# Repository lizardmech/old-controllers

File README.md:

# old-controllers
Footprints located in footprint.zip file unzip to same dir
Schematics are complete chaos may not resemble any of the actual designs, I just threw things into them and did most of the work in PCB editor.

All of these require external capacitors and usually a 15v powersupply in addition to primary supply.
horizontal & BJT PCB small 50mm x 100mm with 12 mosfets and allegro current sense. Probably works but has many less than ideal layout issues.

Sept PCB Large 2 layer PCB with isolated SI8920 current sensors, works very nicely however SI8920 needs complex opamps to be used with cheaper MCUs. Curremt sense on phase A + C. Causes issue with instaspin which expects phase A + B in 2 sensor mode. Lacks any enable or disable pin on gate drivers, attach power without MCU driving them low = bang!
Sept12 & gan same board with space for 12 mosfets and 12 GaNfets should work but untested.

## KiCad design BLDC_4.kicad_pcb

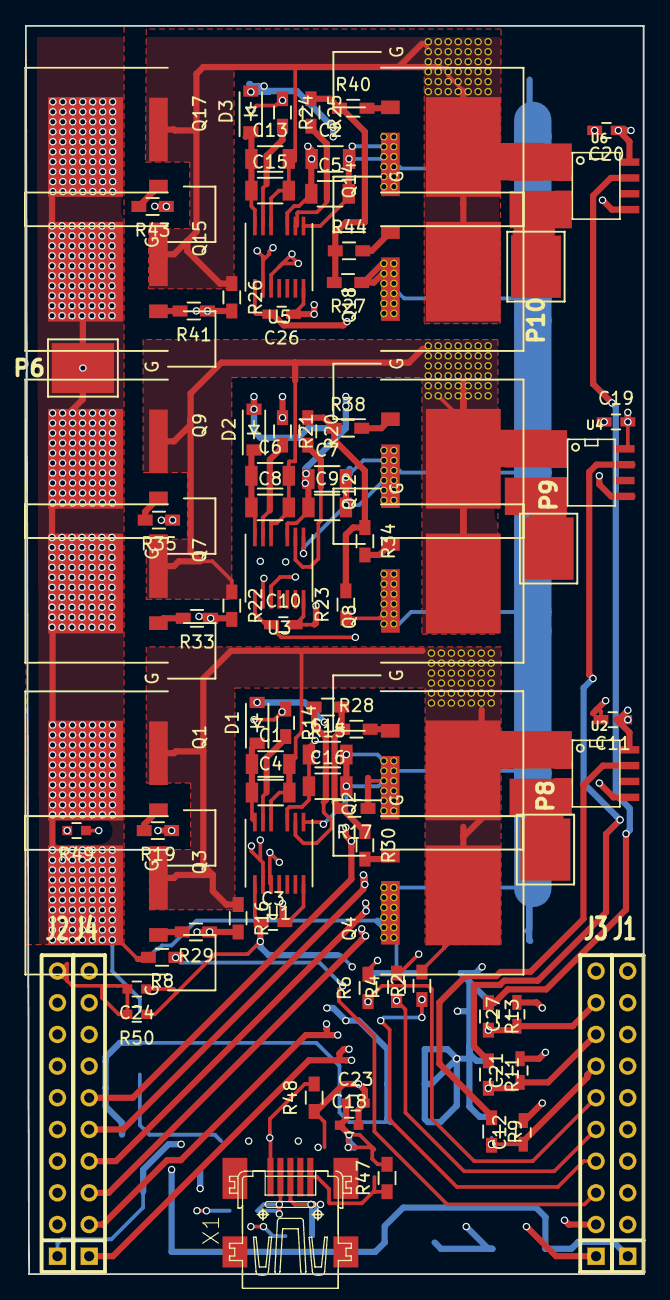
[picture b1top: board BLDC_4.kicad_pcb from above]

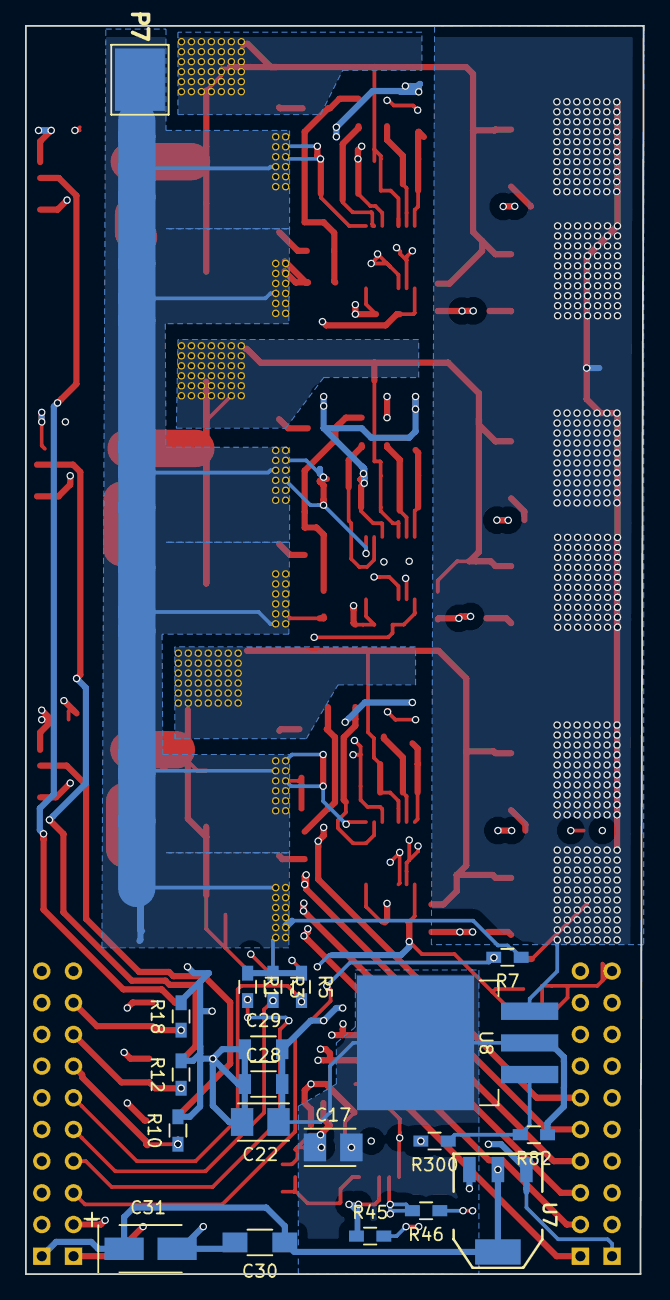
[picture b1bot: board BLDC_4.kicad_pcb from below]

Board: 4 copper layers, 49.5 x 100.1 mm, 109 parts (20 on the bottom side), 62 nets.

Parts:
C1, C2, C6, C7, C13, C14: 0.1uf; C_1206
C3, C10, C11, C12, C19, C20, C21, C26, C27: 0.1uf; C_0603_HandSoldering
C4, C5, C8, C9, C15, C16, C28, C29: 10uf; C_1206
C17, C22: 100uf; TantalC_SizeB_EIA-3528_Reflow
C18, C23, C24: 10uf; C_0603
C30: 2.2uf; C_1206_HandSoldering
C31: 100uf; TantalC_SizeB_EIA-3528_HandSoldering
D1, D2, D3: DFLS1150-7; SOD-123
J1: Ti_Booster_40_J1; SIL-10J1
J2: Ti_Booster_40_J2; SIL-10J2
J3: Ti_Booster_40_J3; SIL-10J3
J4: Ti_Booster_40_J4; SIL-10J4
P6: IN+; 1PAD_4x5mm
P7: IN-; 1PAD_4x5mm
P8: MOTOR3; 1PAD_4x5mm
P9: MOTOR2; 1PAD_4x5mm
P10: MOTOR1; 1PAD_4x5mm
Q1, Q2, Q3, Q4, Q7, Q8, Q9, Q12, Q14, Q15, Q17, Q18: FDMT-800; PQFN-8L-FET
R1, R3, R5, R7: 1.3K; R_0603_HandSoldering
R2, R4, R6, R8: 39K; R_0603_HandSoldering
R9, R11, R13: 2k; R_0603_HandSoldering
R10, R12, R18: 3.9k; R_0603_HandSoldering
R14, R15, R20, R21, R24, R25: 10R; R_0603_HandSoldering
R16, R17, R22, R23, R26, R27: 39k; R_0603_HandSoldering
R19, R28, R29, R30, R33, R34, R35, R38, R40, R41, R43, R44, R45, R46: R22; R_0603_HandSoldering
R47: R0; R_0603_HandSoldering
R48: r0; R_0603_HandSoldering
R49: NTC10K; C_0603
R50: 10K; C_0603
R82: R; R_0603_HandSoldering
R300: R_Small; R_0603_HandSoldering
U1, U3, U5: ADuM7223; LGA-13
U2, U4, U6: ACS723; ACS723_40
U7: NCP1117ST33T3G; SOT-223
U8: tl783; TO-263-3Lead
X1: MINI-USB-SCHIELD-32005-201; con-cypressindustries-32005-201

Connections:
+3V3: C30.1, C31.1, J1.1, R49.1, U7.2
+5V: C3.2, C10.2, C11.1, C17.1, C18.1, C19.2, C20.1, C23.1, C26.1, J3.1, R47.2, U1.7, U2.8, U3.7, U4.8, U5.7, U6.8, U7.3
/Power MOSFETS/CurrentA: C12.1, J3.7, R9.2, R10.1
/Power MOSFETS/CurrentB: C21.1, J3.8, R11.2, R12.1
/Power MOSFETS/CurrentC: C27.1, J3.9, R13.2, R18.1
/Power MOSFETS/H1_VS: C1.2, C4.2, Q1.2, Q2.1, Q3.2, Q4.1, R2.2, R16.1, U1.11, U2.1, U2.2
/Power MOSFETS/H2_VS: C6.2, C8.2, Q7.2, Q8.1, Q9.2, Q12.1, R4.2, R22.1, U3.11, U4.1, U4.2
/Power MOSFETS/H3_VS: C13.2, C15.2, Q14.1, Q15.2, Q17.2, Q18.1, R6.2, R26.1, U5.11, U6.1, U6.2
/Power MOSFETS/M_H1: J4.1, U1.2
/Power MOSFETS/M_H2: J4.3, U3.2
/Power MOSFETS/M_H3: J4.5, U5.2
/Power MOSFETS/M_L1: J4.2, U1.3
/Power MOSFETS/M_L2: J4.4, U3.3
/Power MOSFETS/M_L3: J4.6, U5.3
/Power MOSFETS/PHASE_1: P8.1, U2.3, U2.4
/Power MOSFETS/PHASE_2: P9.1, U4.3, U4.4
/Power MOSFETS/PHASE_3: P10.1, U6.3, U6.4
GND: C2.2, C3.1, C5.2, C7.2, C9.2, C10.1, C11.2, C12.2, C14.2, C16.2, C17.2, C18.2, C19.1, C20.2, C21.2, C22.2, C23.2, C24.1, C26.2, C27.2, C28.1, C29.1, C30.2, C31.2, J2.1, J3.2, P7.1, Q2.2, Q4.2, Q8.2, Q12.2, Q14.2, Q18.2, R1.1, R3.1, R5.1, R7.1, R10.2, R12.2, R17.1, R18.2, R23.1, R27.1, R48.1, R50.1, R300.2, U1.1, U1.8, U2.5, U3.1, U3.8, U4.5, U5.1, U5.8, U6.5, U7.1
unnamed: C1.1, C4.1, D1.1, U1.13
unnamed: C6.1, C8.1, D2.1, U3.13
unnamed: C13.1, C15.1, D3.1, U5.13
unnamed: C24.2, J2.10, R49.2, R50.2
unnamed: J2.2, J2.3, R45.2
unnamed: J2.4, J2.5, R46.1
unnamed: J3.3, R7.2, R8.1
unnamed: J3.4, R1.2, R2.1
unnamed: J3.5, R3.2, R4.1
unnamed: J3.6, R5.2, R6.1
unnamed: Q1.3, R19.2
unnamed: Q2.3, R28.2
unnamed: Q3.3, R29.2
unnamed: Q4.3, R30.2
unnamed: Q7.3, R33.2
unnamed: Q8.3, R34.2
unnamed: Q9.3, R35.2
unnamed: Q12.3, R38.2
unnamed: Q14.3, R40.2
unnamed: Q15.3, R41.2
unnamed: Q17.3, R43.2
unnamed: Q18.3, R44.2
unnamed: R9.1, U2.7
unnamed: R11.1, U4.7
unnamed: R13.1, U6.7
unnamed: R14.1, R16.2, R19.1, R29.1
unnamed: R14.2, U1.12
unnamed: R15.1, R17.2, R28.1, R30.1
unnamed: R15.2, U1.9
unnamed: R20.1, R23.2, R34.1, R38.1
unnamed: R20.2, U3.9
unnamed: R21.1, R22.2, R33.1, R35.1
unnamed: R21.2, U3.12
unnamed: R24.1, R26.2, R41.1, R43.1
unnamed: R24.2, U5.12
unnamed: R25.1, R27.2, R40.1, R44.1
unnamed: R25.2, U5.9
unnamed: R45.1, X1.3
unnamed: R46.2, X1.2
unnamed: R47.1, X1.5
unnamed: R48.2, X1.1
unnamed: R82.2, R300.1, U8.1
VDD: C2.1, C5.1, C7.1, C9.1, C14.1, C16.1, C22.1, C28.2, C29.2, D1.2, D2.2, D3.2, R82.1, U1.10, U3.10, U5.10, U8.2, U8.4
V_SUPPLY: P6.1, Q1.1, Q3.1, Q7.1, Q9.1, Q15.1, Q17.1, R8.2, U8.3

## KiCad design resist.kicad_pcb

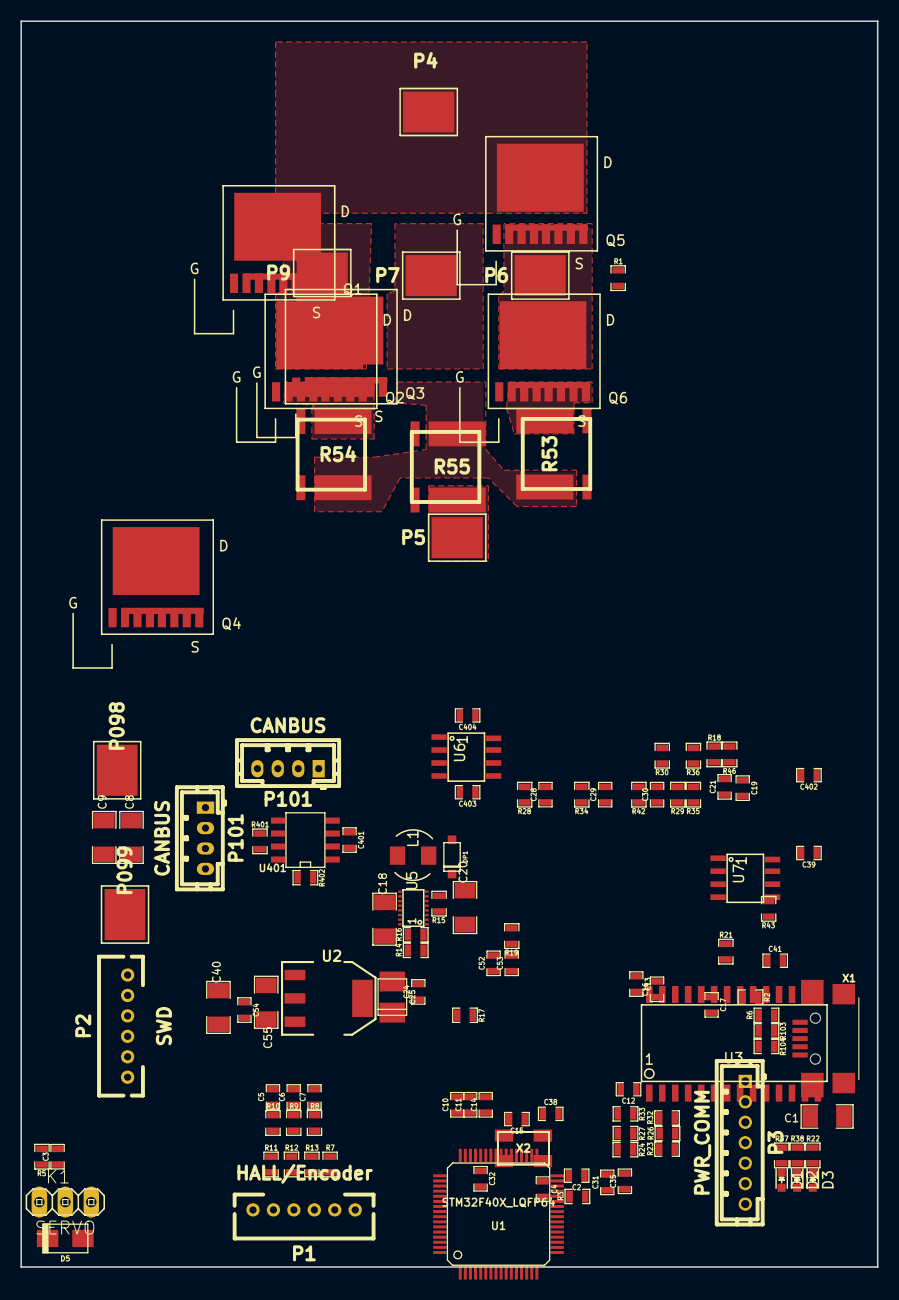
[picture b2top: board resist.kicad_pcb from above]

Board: 4 copper layers, 83.8 x 121.9 mm, 119 parts (0 on the bottom side), 85 nets, no tracks yet.

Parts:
C1, C8, C9, C40: 10u,50V; SMD-1206
C2, C3, C32: 100n; SMD-0603_c
C4, C5, C6, C7: 4n7; SMD-0603_c
C10, C11, C12, C13, C14, C16, C17, C24, C31, C35, C41, C401: 2.2u; SMD-0603_c
C15, C38: 15p; SMD-0603_c
C18, C55: 4.7uF/6.3v; SMD-1206
C19: 1n; SMD-0603_c
C20: 10uF/16V; SMD-1206
C21: 6.8n; SMD-0603_c
C25: 100u; c_tant_B
C28, C29, C30: 220n; SMD-0603_c
C39, C403: 0.1uF; SMD-0603_c
C52: 10u; SMD-0603_c
C53, C54: 100nF; SMD-0603_c
C402, C404: 2.2n; SMD-0603_c
D1: GREEN; LED_0603
D2: RED; LED_0603
D3: LED; LED_0603
D5: TVS 5V; do214ac
DP1: MBR0530; sod123
K1: SERVO; pinhead-1X03
L1: 1.2uH (ELL-4GG1R2N); ELL-4GG
P1: HALL/Encoder; MICRO_JST_6
P2: SWD; MICRO_JST_6
P3: PWR_COMM; b7b-ph-kl
P4: IN+; 1PAD_4x5mm
P5: IN-; 1PAD_4x5mm
P6: MOTOR1; 1PAD_4x5mm
P7: MOTOR2; 1PAD_4x5mm
P9: MOTOR3; 1PAD_4x5mm
P098: CAN pwr gnd; 1PAD_4x5mm
P099: CAN power; 1PAD_4x5mm
P101, P101#2: CANBUS; b4b-ph-kl
Q1, Q2, Q3, Q4, Q5, Q6: FDBL0630N150; P-PG-HSOF-08
R1: NTC 10k; SMD-0603_r
R2, R7, R8, R9, R10, R17, R402: 10k; SMD-0603_r
R3, R23, R26, R30, R32, R36, R46: 39k; SMD-0603_r
R5, R11, R12, R13, R22, R24, R27, R33: 2k2; SMD-0603_r
R6: 0R; SMD-0603_r
R14: 4.99k; SMD-0603_r
R15: 90.9k; SMD-0603_r
R16: 3.01k; SMD-0603_r
R18: 1k; SMD-0603_r
R19: 1.8k; SMD-0603_r
R21: 8.04K; SMD-0603_r
R28, R29, R34, R35, R42, R43: 4R7; SMD-0603_r
R37, R38: 100R; SMD-0603_r
R53, R54, R55: 0.0005R/5W; WSLP2726
R103, R104: 22R; SMD-0603_r
R401: NI; SMD-0603_r
U1: STM32F40X_LQFP64; lqfp64_pad_mod
U2: TC2117; SOT-223
U3: 6EDL04I06PT; 6EDL04N0
U5: AAT1210
U6, U7: INA282
U401: SN65HVD232; SOIC-8-W
X1: MINI-USB-SHIELD-32005-201; USB-UX60R-MB-5ST
X2: 8MHz 10ppm; Crystal_5x3mm

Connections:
+5V: C1.2, C8.2, C9.2, C18.1, C40.2, C54.2, C55.1, D5.2, K1.2, P1.1, P3.1, P099.1, P101.4, P101#2.4, R6.2, U2.3, U5.12, U5.13, U5.14, U5.15, U5.16
/CAN bus transceiver/CANH: P101.3, P101#2.3, R401.1, U401.7
/CAN bus transceiver/CANL: P101.2, P101#2.2, R401.2, U401.6
/CAN bus transceiver/CAN_RX: U1.61, U401.4
/CAN bus transceiver/CAN_TX: U1.62, U401.1
/Filters/HALL1_IN: P1.3, R8.1, R13.1
/Filters/HALL1_OUT: C7.1, R8.2, U1.58
/Filters/HALL2_IN: P1.4, R9.1, R12.1
/Filters/HALL2_OUT: C6.1, R9.2, U1.59
/Filters/HALL3_IN: P1.5, R10.1, R11.1
/Filters/HALL3_OUT: C5.1, R10.2, U1.52
/Filters/TEMP_IN: C4.2, P1.2, R7.1, U1.8
/MCU/ADC_TEMP: C41.1, R1.2, R2.1, U1.17
/MCU/AN_IN: C2.2, R3.2, U1.10
/MCU/BR_S01: U1.26, U6.5
/MCU/BR_S02: U1.27, U7.5
/MCU/EN_GATE: U1.51, U3.10
/MCU/FAULT: R17.2, U1.53, U3.8
/MCU/H1: U1.43, U3.2
/MCU/H2: U1.42, U3.3
/MCU/H3: U1.41, U3.4
/MCU/L1: U1.36, U3.5
/MCU/L2: U1.35, U3.6
/MCU/L3: U1.34, U3.7
/MCU/LED_GREEN: R37.2, U1.24
/MCU/LED_RED: R38.2, U1.25
/MCU/MISO_ADC_EXT2: P3.7, U1.22
/MCU/RX_SCL_MOSI: P3.6, U1.23, U1.29, U1.38
/MCU/SCK_ADC_EXT: P3.4, U1.21
/MCU/SENS1: R23.2, R24.2, U1.16
/MCU/SENS2: R26.2, R27.2, U1.15
/MCU/SENS3: R32.2, R33.2, U1.14
/MCU/SERVO: C3.2, R5.1, U1.57
/MCU/TX_SDA_NSS: P3.5, U1.20, U1.30, U1.37
/MCU/USB_DM: R103.1, U1.44
/MCU/USB_DP: R104.1, U1.45
/Mosfet driver/H1_LOW: Q2.S, R30.1, R36.1, R54.2
/Mosfet driver/H1_VS: C28.1, P9.1, Q1.S, Q2.D, R23.1, U3.26
/Mosfet driver/H2_LOW: Q4.S, R18.2, R53.2, R54.1, R55.2, U3.13
/Mosfet driver/H2_VS: C29.1, P7.1, Q3.S, Q4.D, R26.1, U3.22
/Mosfet driver/H3_LOW: Q6.S, R46.1, R53.1
/Mosfet driver/H3_VS: C30.1, P6.1, Q5.S, Q6.D, R32.1, U3.18
/Mosfet driver/M_H1: R28.2, U3.27
/Mosfet driver/M_H2: R34.2, U3.23
/Mosfet driver/M_H3: R42.2, U3.19
/Mosfet driver/M_L1: R29.2, U3.16
/Mosfet driver/M_L2: R35.2, U3.15
/Mosfet driver/M_L3: R43.2, U3.14
GND: C1.1, C2.1, C3.1, C4.1, C5.2, C6.2, C7.2, C8.1, C9.1, C10.1, C11.1, C12.1, C13.1, C14.1, C15.2, C16.2, C17.2, C18.2, C19.2, C20.2, C21.1, C24.2, C25.2, C31.1, C32.1, C35.1, C38.2, C39.2, C40.1, C41.2, C52.1, C53.1, C54.1, C55.2, C401.2, C403.2, D1.2, D2.2, D3.2, D5.1, K1.3, P1.6, P2.3, P3.3, P5.1, P098.1, P101.1, P101#2.1, R2.2, R14.2, R24.1, R27.1, R33.1, R55.1, R402.2, U1.12, U1.18, U1.60, U1.63, U2.1, U3.12, U5.5, U5.6, U5.7, U5.8, U6.2, U6.3, U6.4, U7.2, U7.3, U7.4, U401.2, X1.5, X2.3
NRST: C32.2, P2.5, U1.7
unnamed: C15.1, U1.5, X2.1
unnamed: C16.1, U1.31
unnamed: C17.1, U1.47
unnamed: C19.1, R18.1, R21.2, U3.9
unnamed: C21.2, R19.1, U3.11
unnamed: C28.2, U3.28
unnamed: C29.2, U3.24
unnamed: C30.2, U3.20
unnamed: C38.1, U1.6, X2.2
unnamed: C402.1, R53.3, U7.8
unnamed: C402.2, R53.4, U7.1
unnamed: C404.1, R54.4, U6.8
unnamed: C404.2, R54.3, U6.1
unnamed: D1.1, R37.1
unnamed: D2.1, R38.1
unnamed: D3.1, R22.1
unnamed: DP1.1, L1.1, U5.9, U5.10
unnamed: K1.1, R5.2
unnamed: L1.2, U5.1, U5.2
unnamed: Q1.G, R28.1
unnamed: Q2.G, R29.1, R30.2
unnamed: Q3.G, R34.1
unnamed: Q4.G, R35.1, R36.2
unnamed: Q5.G, R42.1
unnamed: Q6.G, R43.1, R46.2
unnamed: R14.1, R16.2, U5.4
unnamed: R15.2, R16.1, U5.3
unnamed: R103.2, X1.2
unnamed: R104.2, X1.3
unnamed: R402.1, U401.8
SWCLK: P2.2, U1.49
SWDIO: P2.4, U1.46
VCC: C10.2, C11.2, C12.2, C13.2, C14.2, C24.1, C25.1, C31.2, C35.2, C39.1, C401.1, C403.1, P2.1, P3.2, R1.1, R7.2, R11.2, R12.2, R13.2, R17.1, R21.1, R22.2, U1.1, U1.13, U1.19, U1.32, U1.48, U1.64, U2.2, U6.6, U6.7, U7.6, U7.7, U401.3
VDD: C20.1, C52.2, C53.2, DP1.2, R15.1, R19.2, U3.1
V_SUPPLY: P4.1, Q1.D, Q3.D, Q5.D, R3.1

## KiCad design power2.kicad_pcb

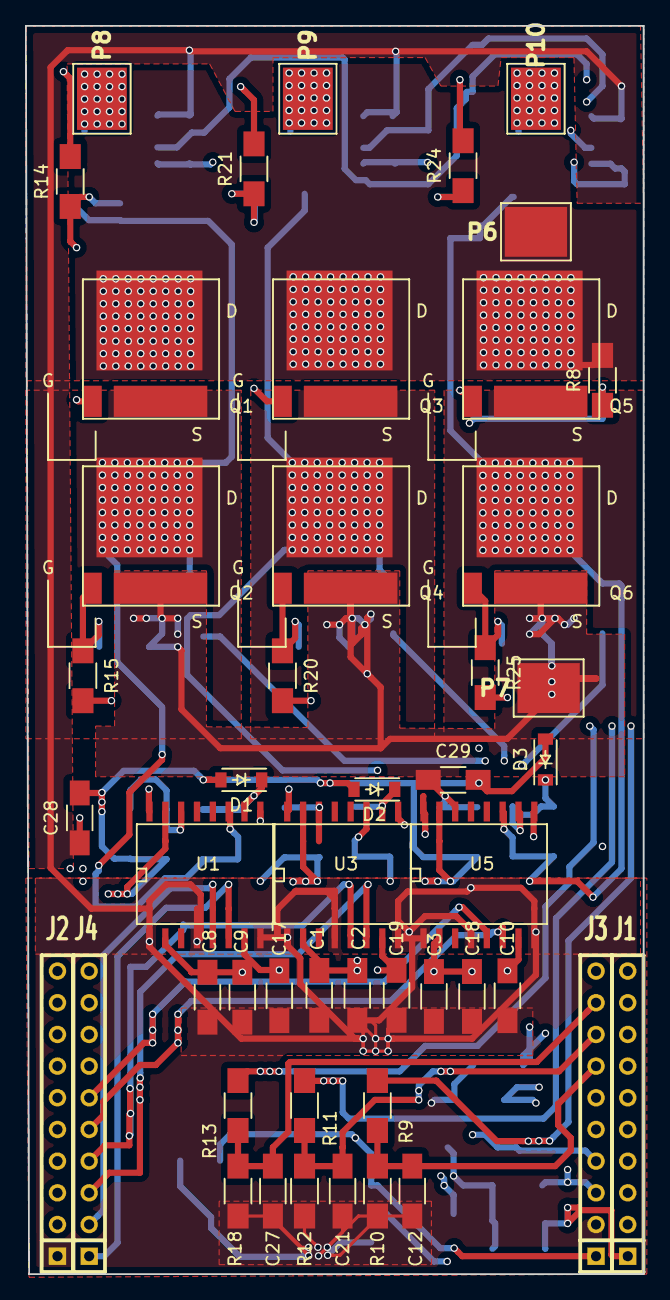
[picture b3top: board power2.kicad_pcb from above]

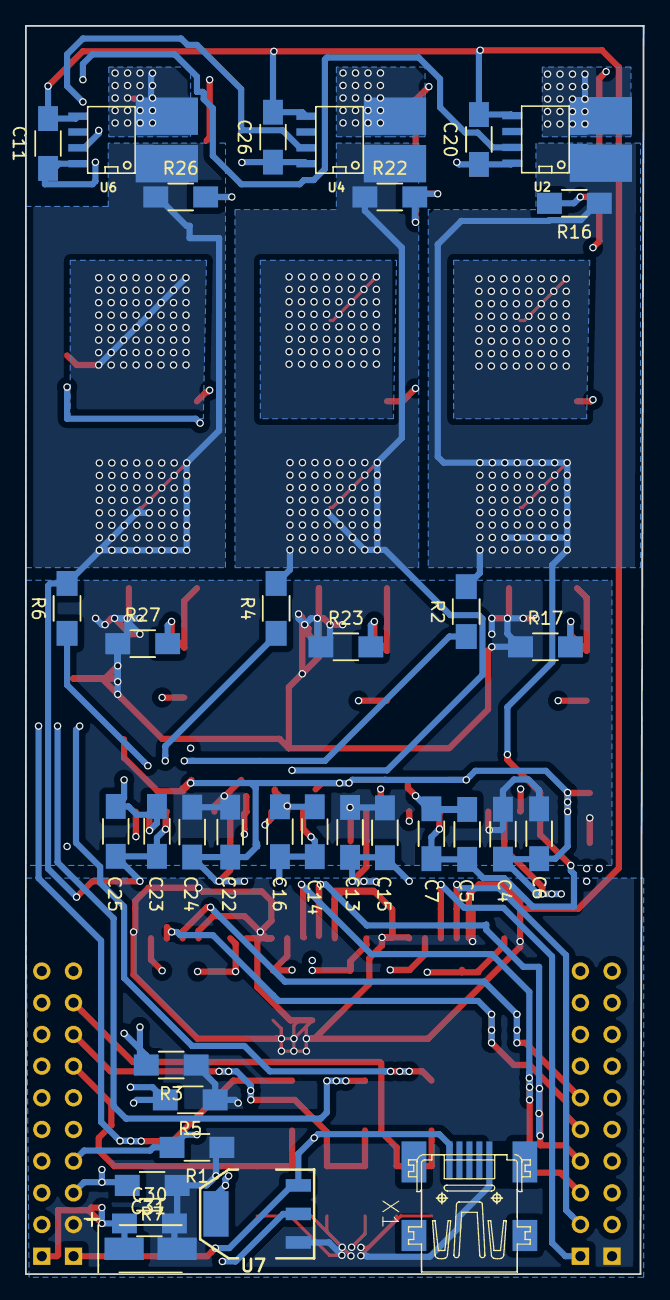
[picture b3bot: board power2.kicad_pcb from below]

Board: 4 copper layers, 49.5 x 100.1 mm, 83 parts (35 on the bottom side), 42 nets.

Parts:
C1, C3, C4, C5, C8, C10, C11, C12, C13, C14, C17, C19, C20, C21, C22, C23, C26, C27: 0.1uf; C_1206_HandSoldering
C2, C6, C9, C15, C18, C24, C28, C29: 10uf; C_1206_HandSoldering
C7, C16, C25: 1uf; C_1206_HandSoldering
C30: 2.2uf; C_1206_HandSoldering
C31: 100uf; TantalC_SizeB_EIA-3528_HandSoldering
D1, D2, D3: DFLS1150-7; SOD-123
J1: Ti_Booster_40_J1; SIL-10J1
J2: Ti_Booster_40_J2; SIL-10J2
J3: Ti_Booster_40_J3; SIL-10J3
J4: Ti_Booster_40_J4; SIL-10J4
P6: IN+; 1PAD_4x5mm
P7: IN-; 1PAD_4x5mm
P8: MOTOR3; 1PAD_4x5mm
P9: MOTOR2; 1PAD_4x5mm
P10: MOTOR1; 1PAD_4x5mm
Q1, Q2, Q3, Q4, Q5, Q6: FDBL0630N150; P-PG-HSOF-08
R1, R3, R5, R7: 1.3K; R_1206_HandSoldering
R2, R4, R6, R8: 39K; R_1206_HandSoldering
R9, R11, R13: 39R; R_1206_HandSoldering
R10, R12, R18: 20R; R_1206_HandSoldering
R14, R15, R20, R21, R24, R25: 100R; R_1206_HandSoldering
R16, R17, R22, R23, R26, R27: 39k; R_1206_HandSoldering
U1, U3, U5: ADUm530; SO-16-W_handsolder
U2, U4, U6: ACS723; ACS723_40
U7: NCP1117ST33T3G; SOT-223
X1: MINI-USB-SCHIELD-32005-201; con-cypressindustries-32005-201

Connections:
+3V3: C30.1, C31.1, J1.1, U7.2
+5V: C1.2, C2.2, C3.1, C8.2, C9.2, C10.1, C11.1, C17.2, C18.2, C19.1, C20.1, C26.1, J3.1, U1.2, U1.7, U2.8, U3.2, U3.7, U4.8, U5.2, U5.7, U6.8, U7.3, X1.1
+15V: C4.1, C6.1, C13.1, C15.1, C22.1, C24.1, C28.2, C29.2, D1.2, D2.2, D3.2, U1.15, U3.15, U5.15
/Power MOSFETS/CurrentA: C12.1, J3.7, R9.2, R10.1
/Power MOSFETS/CurrentB: C21.1, J3.8, R11.2, R12.1
/Power MOSFETS/CurrentC: C27.1, J3.9, R13.2, R18.1
/Power MOSFETS/H1_VS: C5.1, C7.1, Q1.S, Q2.D, R2.2, R16.1, U1.11, U2.1, U2.2
/Power MOSFETS/H2_VS: C14.1, C16.1, Q3.S, Q4.D, R4.2, R22.1, U3.11, U4.1, U4.2
/Power MOSFETS/H3_VS: C23.1, C25.1, Q5.S, Q6.D, R6.2, R26.1, U5.11, U6.1, U6.2
/Power MOSFETS/M_H1: J4.1, U1.6
/Power MOSFETS/M_H2: J4.3, U3.6
/Power MOSFETS/M_H3: J4.5, U5.6
/Power MOSFETS/M_L1: J4.2, U1.5
/Power MOSFETS/M_L2: J4.4, U3.5
/Power MOSFETS/M_L3: J4.6, U5.5
/Power MOSFETS/PHASE_1: P8.1, U2.3, U2.4
/Power MOSFETS/PHASE_2: P9.1, U4.3, U4.4
/Power MOSFETS/PHASE_3: P10.1, U6.3, U6.4
GND: C1.1, C2.1, C3.2, C4.2, C6.2, C8.1, C9.1, C10.2, C11.2, C12.2, C13.2, C15.2, C17.1, C18.1, C19.2, C20.2, C21.2, C22.2, C24.2, C26.2, C27.2, C28.1, C29.1, C30.2, C31.2, J2.1, J3.2, P7.1, Q2.S, Q4.S, Q6.S, R1.1, R3.1, R5.1, R7.1, R10.2, R12.2, R17.1, R18.2, R23.1, R27.1, U1.1, U1.4, U1.8, U1.14, U2.5, U3.1, U3.4, U3.8, U3.14, U4.5, U5.1, U5.4, U5.8, U5.14, U6.5, U7.1, X1.5
unnamed: C5.2, C7.2, D1.1, U1.10
unnamed: C14.2, C16.2, D2.1, U3.10
unnamed: C23.2, C25.2, D3.1, U5.10
unnamed: J3.3, R7.2, R8.1
unnamed: J3.4, R1.2, R2.1
unnamed: J3.5, R3.2, R4.1
unnamed: J3.6, R5.2, R6.1
unnamed: Q1.G, R14.1, R16.2
unnamed: Q2.G, R15.1, R17.2
unnamed: Q3.G, R21.1, R22.2
unnamed: Q4.G, R20.1, R23.2
unnamed: Q5.G, R24.1, R26.2
unnamed: Q6.G, R25.1, R27.2
unnamed: R9.1, U2.7
unnamed: R11.1, U4.7
unnamed: R13.1, U6.7
unnamed: R14.2, U1.9
unnamed: R15.2, U1.16
unnamed: R20.2, U3.16
unnamed: R21.2, U3.9
unnamed: R24.2, U5.9
unnamed: R25.2, U5.16
V_SUPPLY: P6.1, Q1.D, Q3.D, Q5.D, R8.2

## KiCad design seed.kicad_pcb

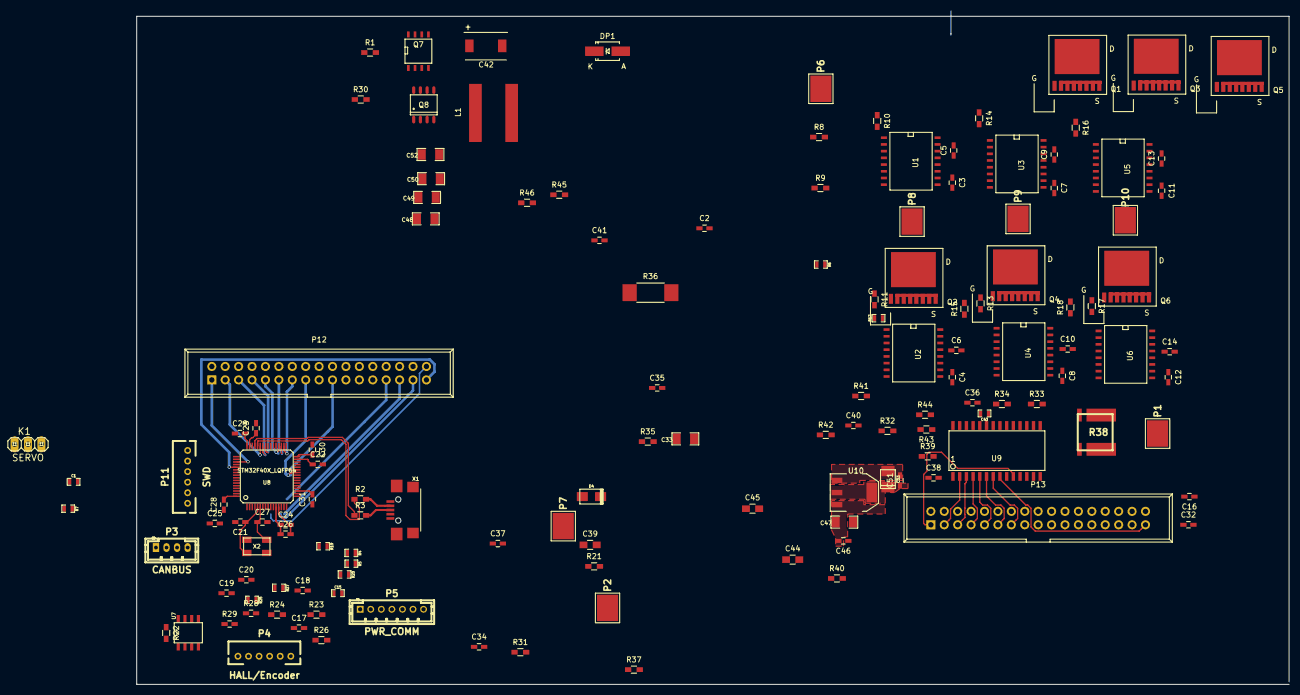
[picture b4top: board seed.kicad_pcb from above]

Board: 4 copper layers, 218.2 x 127.5 mm, 136 parts (0 on the bottom side), 114 nets.

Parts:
C1: 100n; SMD-0603_c
C2, C25: 100n; C_0603_HandSoldering
C3, C4, C7, C8, C11, C12: 0.1uf; C_0603_HandSoldering
C5, C6, C9, C10, C13, C14: 1nf; C_0603_HandSoldering
C15: 2.2u; SMD-0603_c
C16, C22, C23, C24, C26, C28, C29, C30, C31, C32, C51: 2.2u; C_0603_HandSoldering
C17, C18, C19, C20: 4n7; C_0603_HandSoldering
C21, C27: 15p; C_0603_HandSoldering
C33: 47uF/6.3v; SMD-1206
C34: 6.8n; C_0603_HandSoldering
C35: 0.1uF; C_0603_HandSoldering
C36: 1n; C_0603_HandSoldering
C37, C46: 100nF; C_0603_HandSoldering
C38: 10u; C_0603_HandSoldering
C39: 0.01uf; C_0805_HandSoldering
C40, C41: 220n; C_0603_HandSoldering
C42: 180uF; 180ufcap
C43: 220n; SMD-0603_c
C44: 0.015uF; C_0805_HandSoldering
C45: 820pF; C_0805_HandSoldering
C47: 4.7uF/6.3v; SMD-1206
C48, C49, C50, C52: 10u,50V; SMD-1206
C53: 100u; c_tant_B
D4: TVS 5V; do214ac
DP1: B230A-13-F; SMA_Handsoldering
K1: SERVO; pinhead-1X03
L1: 4.7 uH (ELL-4GG1R2N); coilworks4.7uF
P1: CAN pwr gnd; 1PAD_4x5mm
P2: CAN power; 1PAD_4x5mm
P3: CANBUS; b4b-ph-kl
P4: HALL/Encoder; MICRO_JST_6
P5: PWR_COMM; b7b-ph-kl
P6: IN+; 1PAD_4x5mm
P7: IN-; 1PAD_4x5mm
P8: MOTOR3; 1PAD_4x5mm
P9: MOTOR2; 1PAD_4x5mm
P10: MOTOR1; 1PAD_4x5mm
P11: SWD; MICRO_JST_6
P12, P13: CONN_02X17; IDC_Header_Straight_34pins
Q1, Q2, Q3, Q4, Q5, Q6: FDBL0630N150; P-PG-HSOF-08
Q7: lm3478; SOIC-8-N
Q8: IRF8721PBF-1; SO-8
R1: 0R; R_0603_HandSoldering
R2, R3: 22R; R_0603_HandSoldering
R4, R5: 100R; SMD-0603_r
R6, R7, R25: 2k2; SMD-0603_r
R8, R15, R18, R41, R43, R45: 39k; R_0603_HandSoldering
R9, R24, R26, R42, R44, R46: 2k2; R_0603_HandSoldering
R10, R11, R13, R14, R16, R17: 4R7; R_0603_HandSoldering
R12: 39k; SMD-0603_r
R19: NTC 10k; SMD-0603_r
R20, R27: 10k; SMD-0603_r
R21: NI; R_0603_HandSoldering
R22, R23, R32: 10k; R_0603_HandSoldering
R28, R29: 10k; C_0603_HandSoldering
R30: 26.7k; R_0603_HandSoldering
R31: 1.8k; R_0603_HandSoldering
R33: 1k; R_0603_HandSoldering
R34: 8.04K; R_0603_HandSoldering
R35: 100 Ohm; R_0603_HandSoldering
R36: 10 mOhm; R_2512_HandSoldering
R37: 1000ohm; R_0603_HandSoldering
R38: 0.0005R/5W; WSLP2726
R39: 11k; R_0603_HandSoldering
R40: 5.76k; R_0603_HandSoldering
U1, U2, U3, U4, U5, U6: allegro; SO-16-W
U7: SN65HVD232; SOIC-8-W
U8: STM32F40X_LQFP64; lqfp64_pad_mod
U9: 6EDL04I06PT; 6EDL04N0
U10: TC2117; SOT-223
X1: MINI-USB-SHIELD-32005-201; USB-UX60R-MB-5ST
X2: 8MHz 10ppm; Crystal_5x3mm

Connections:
+5V: C33.1, C35.1, C46.2, C47.1, D4.2, K1.2, L1.2, P2.1, P3.4, P4.1, P5.1, Q7.8, R1.2, U10.3
/CAN bus transceiver/CANH: P3.3, R21.1, U7.7
/CAN bus transceiver/CANL: P3.2, R21.2, U7.6
/CAN bus transceiver/CAN_RX: U7.4, U8.61
/CAN bus transceiver/CAN_TX: U7.1, U8.62
/Filters/HALL1_IN: P4.3, R26.1, R29.1
/Filters/HALL1_OUT: C20.1, R29.2, U8.58
/Filters/HALL2_IN: P4.4, R25.1, R28.1
/Filters/HALL2_OUT: C19.1, R28.2, U8.59
/Filters/HALL3_IN: P4.5, R24.1, R27.1
/Filters/HALL3_OUT: C18.1, R27.2, U8.52
/Filters/TEMP_IN: C17.2, P4.2, R23.1, U8.8
/MCU/ADC_TEMP: C15.1, R19.2, R20.1, U8.17
/MCU/AN_IN: P12.34, U8.10
/MCU/BR_S01: P12.15, U8.26
/MCU/BR_S02: P12.19, U8.27
/MCU/EN_GATE: P12.1, U8.51
/MCU/FAULT: P12.33, U8.53
/MCU/H1: P12.3, U8.43
/MCU/H2: P12.5, U8.42
/MCU/H3: P12.7, U8.41
/MCU/L1: P12.9, U8.36
/MCU/L2: P12.11, U8.35
/MCU/L3: P12.13, U8.34
/MCU/LED_GREEN: R5.2, U8.24
/MCU/LED_RED: R4.2, U8.25
/MCU/MISO_ADC_EXT2: P5.7, U8.22
/MCU/RX_SCL_MOSI: P5.6, U8.23, U8.29, U8.38
/MCU/SCK_ADC_EXT: P5.4, U8.21
/MCU/SENS1: P12.27, U8.16
/MCU/SENS2: P12.29, U8.15
/MCU/SENS3: P12.31, U8.14
/MCU/SERVO: C1.2, R7.1, U8.57
/MCU/TX_SDA_NSS: P5.5, U8.20, U8.30, U8.37
/MCU/USB_DM: R2.1, U8.44
/MCU/USB_DP: R3.1, U8.45
/Mosfet driver/AN_IN: C2.2, P13.34, R8.2, R9.2
/Mosfet driver/EN_GATE: P13.1, U9.10
/Mosfet driver/FAULT: P13.33, R32.2, U9.8
/Mosfet driver/H1: P13.3, U9.2
/Mosfet driver/H1_LOW: R33.2, R38.2, U2.5, U2.6, U2.7, U2.8, U4.5, U4.6, U4.7, U4.8, U6.5, U6.6, U6.7, U6.8, U9.13
/Mosfet driver/H1_VS: C40.1, P8.1, Q2.D, R41.1, U1.5, U1.6, U1.7, U1.8, U9.26
/Mosfet driver/H2: P13.5, U9.3
/Mosfet driver/H2_VS: C43.1, P9.1, Q4.D, R43.1, U3.5, U3.6, U3.7, U3.8, U9.22
/Mosfet driver/H3: P13.7, U9.4
/Mosfet driver/H3_VS: C41.1, P10.1, Q6.D, R45.1, U5.5, U5.6, U5.7, U5.8, U9.18
/Mosfet driver/L1: P13.9, U9.5
/Mosfet driver/L2: P13.11, U9.6
/Mosfet driver/L3: P13.13, U9.7
/Mosfet driver/M_H1: R10.2, U9.27
/Mosfet driver/M_H2: R14.2, U9.23
/Mosfet driver/M_H3: R16.2, U9.19
/Mosfet driver/M_L1: R11.2, U9.16
/Mosfet driver/M_L2: R13.2, U9.15
/Mosfet driver/M_L3: R17.2, U9.14
/Mosfet driver/SENS1: P13.27, R41.2, R42.2
/Mosfet driver/SENS2: P13.29, R43.2, R44.2
/Mosfet driver/SENS3: P13.31, R45.2, R46.2
/connector/SPARE: P12.30, P12.32, P13.32
GND: C1.1, C2.1, C5.2, C6.2, C9.2, C10.2, C13.2, C14.2, C15.2, C16.2, C17.1, C18.2, C19.2, C20.2, C21.2, C22.2, C23.2, C24.1, C25.1, C26.1, C27.2, C28.1, C29.1, C30.1, C31.1, C32.1, C33.2, C34.1, C35.2, C36.2, C37.1, C38.1, C39.2, C42.2, C45.2, C46.1, C47.2, C50.1, C51.2, C52.1, C53.2, D4.1, K1.3, P1.1, P3.1, P4.6, P5.3, P7.1, P11.3, Q7.4, Q7.5, R9.1, R20.2, R22.2, R30.2, R36.2, R37.2, R38.1, R40.2, R42.1, R44.1, R46.1, U1.11, U1.14, U1.15, U2.11, U2.14, U2.15, U3.11, U3.14, U3.15, U4.11, U4.14, U4.15, U5.11, U5.14, U5.15, U6.11, U6.14, U6.15, U7.2, U8.12, U8.18, U8.60, U8.63, U9.12, U10.1, X1.5, X2.3
NRST: C25.2, P11.5, U8.7
unnamed: C3.1, U1.10
unnamed: C4.1, U2.10
unnamed: C5.1, U1.13
unnamed: C6.1, U2.13
unnamed: C7.1, U3.10
unnamed: C8.1, U4.10
unnamed: C9.1, U3.13
unnamed: C10.1, U4.13
unnamed: C11.1, U5.10
unnamed: C12.1, U6.10
unnamed: C13.1, U5.13
unnamed: C14.1, U6.13
unnamed: C21.1, U8.5, X2.1
unnamed: C22.1, U8.31
unnamed: C23.1, U8.47
unnamed: C27.1, U8.6, X2.2
unnamed: C34.2, R31.1, U9.11
unnamed: C36.1, R33.1, R34.2, U9.9
unnamed: C39.1, Q7.1, R35.2
unnamed: C40.2, U9.28
unnamed: C41.2, U9.20
unnamed: C43.2, U9.24
unnamed: C44.1, C45.1, Q7.2
unnamed: C44.2, R40.1
unnamed: C48.1, C49.1
unnamed: C48.2, C49.2
unnamed: C50.2, C52.2
unnamed: DP1.1, L1.1, Q8.5, Q8.6, Q8.7, Q8.8
unnamed: K1.1, R7.2
unnamed: Q1.G, R10.1
unnamed: Q1.S, U1.1, U1.2, U1.3, U1.4
unnamed: Q2.G, R11.1, R12.2
unnamed: Q2.S, R12.1, U2.1, U2.2, U2.3, U2.4
unnamed: Q3.G, R14.1
unnamed: Q3.S, U3.1, U3.2, U3.3, U3.4
unnamed: Q4.G, R13.1, R15.2
unnamed: Q4.S, R15.1, U4.1, U4.2, U4.3, U4.4
unnamed: Q5.G, R16.1
unnamed: Q5.S, U5.1, U5.2, U5.3, U5.4
unnamed: Q6.G, R17.1, R18.2
unnamed: Q6.S, R18.1, U6.1, U6.2, U6.3, U6.4
unnamed: Q7.3, R37.1, R39.2
unnamed: Q7.6, Q8.4
unnamed: Q7.7, R30.1
unnamed: Q8.1, Q8.2, Q8.3, R35.1, R36.1
unnamed: R2.2, X1.2
unnamed: R3.2, X1.3
unnamed: R22.1, U7.8
SWCLK: P11.2, U8.49
SWDIO: P11.4, U8.46
VCC: C3.2, C4.2, C7.2, C8.2, C11.2, C12.2, C16.1, C24.2, C26.2, C28.2, C29.2, C30.2, C31.2, C32.2, C51.1, C53.1, P5.2, P11.1, R6.2, R19.1, R23.2, R24.2, R25.2, R26.2, R32.1, R34.1, U7.3, U8.1, U8.13, U8.19, U8.32, U8.48, U8.64, U10.2
VDD: C37.2, C38.2, C42.1, DP1.2, R31.2, R39.1, U9.1
V_SUPPLY: P6.1, Q1.D, Q3.D, Q5.D, R8.1
